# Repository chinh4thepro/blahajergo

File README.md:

## Hardware
Uses a Nice!Nano V2 (or any compatible microcontroller) as the MCU

Parts list:
- 56x SOD-123 (supports through holes too) 1N4148W diodes
- 56x Kailh 1350 Hotswap Sockets
- 56x Kailh choc v1 or v2 switches (v1's may be a little loose)
- 54x 1u choc keycaps
- 2x 1.5u choc keycaps
- 2x Nice!Nano V2 (sockets too)
- 2x 0.91in 128x32 SSD1306 OLED displays (sockets too)
- 2x 110mAh 301230 lithium batteries with PH 2.00mm connectors
- 2x Alps miniature SPDT switches
- 2x JST PH 2.00mm battery connectors
- 2x Panasonic EVQPUC buttons

## Software
Keymap based/inspired by FlatFootFox's (ImStuBTW) [TypeBoy MKII](https://github.com/ImStuBTW/typeboy_mkii)

Config can be found [here](https://github.com/chinh4thepro/zmk-config-blahajergo/tree/master)

## Design
Planned to have a 3d-printed case and acrylic case.

Traced blahaj image in courtesy of [Sheepy0125](https://github.com/sheepy0125)

## Progress
- [x] Design schematic - Done 2/10/2024
- [x] Name + Logo - Done 2/5/2024
- [x] Design PCB - Done 2/10/2024
- [x] Redesign PCB - Done 5/08/2024
- [x] Order PCB + Parts - Done 2/12/2024
- [x] Reorder PCB - Done 5/9/2024
- [x] Construct PCB - Done 5/17/2024
- [x] Port to ZMK - Done 2/27/2024
- [ ] Design 3d case
- [ ] Design acrylic case

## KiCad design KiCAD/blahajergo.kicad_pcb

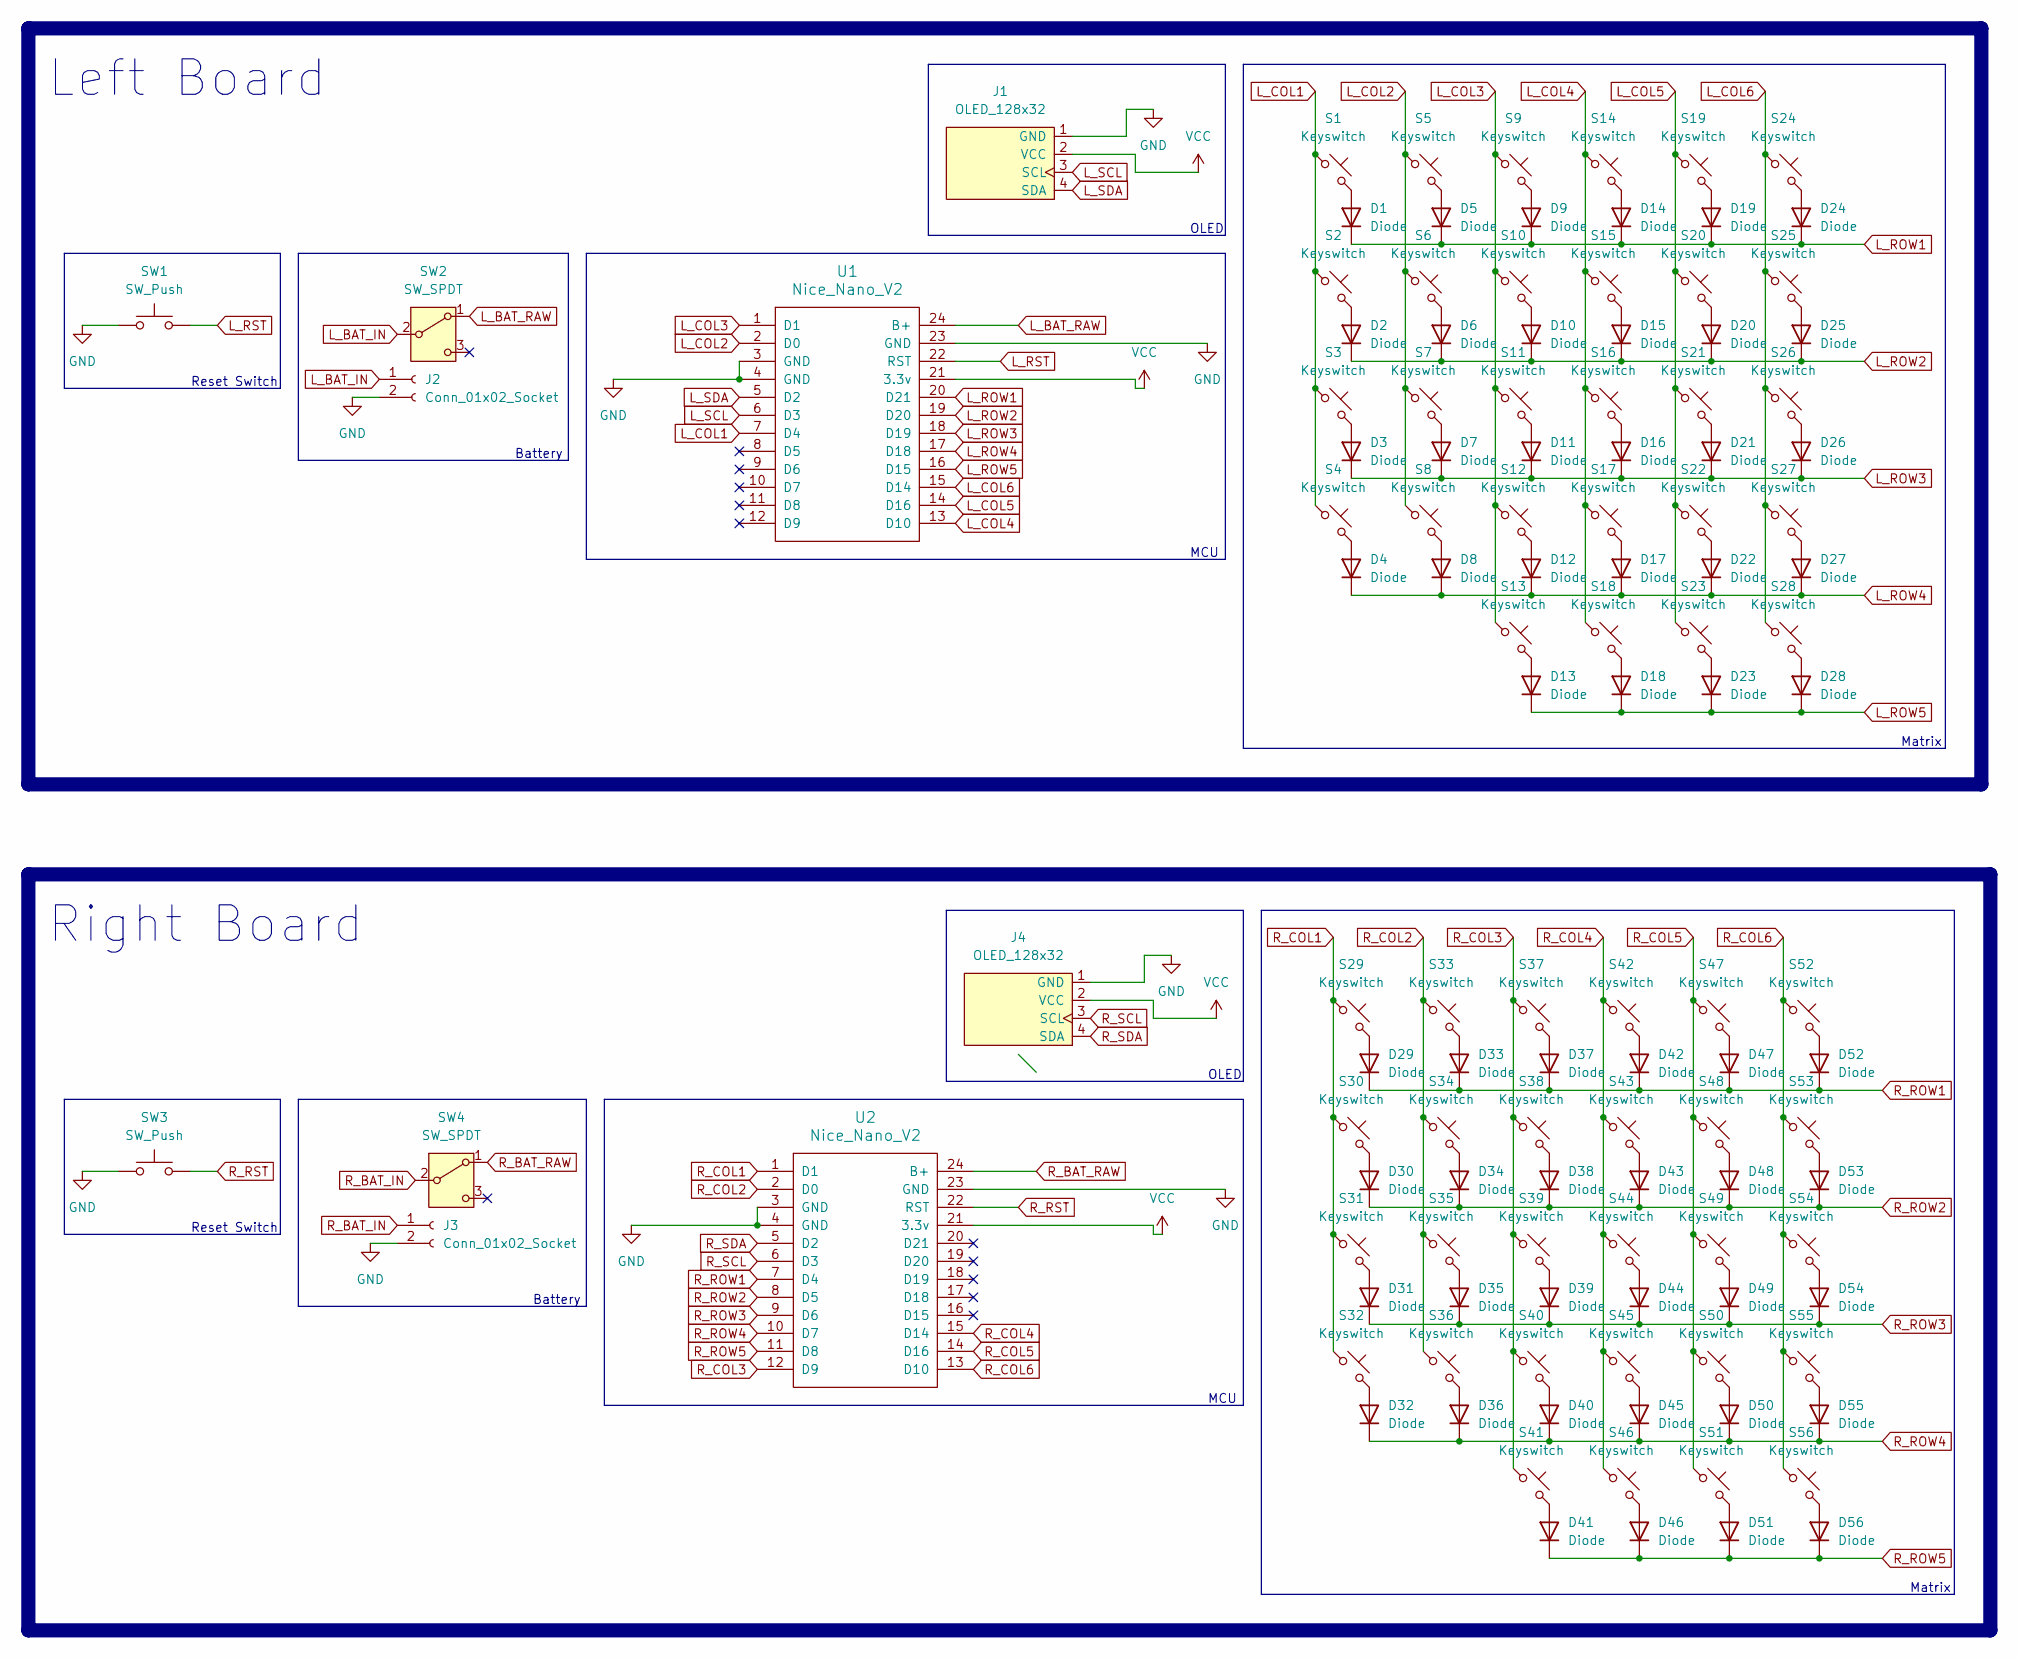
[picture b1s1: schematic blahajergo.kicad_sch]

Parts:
D1, D2, D3, D4, D5, D6, D7, D8, D9, D10, D11, D12, D13, D14, D15, D16, D17, D18, D19, D20, D21, D22, D23, D24, D25, D26, D27, D28, D29, D30, D31, D32, D33, D34, D35, D36, D37, D38, D39, D40, D41, D42, D43, D44, D45, D46, D47, D48, D49, D50, D51, D52, D53, D54, D55, D56: Diode; ComboDiode
J1, J4: OLED_128x32
J2, J3: Conn_01x02_Socket; JST_PH_S2B-PH-K_1x02_P2.00mm_Horizontal
S1, S2, S3, S4, S5, S6, S7, S8, S9, S10, S11, S12, S13, S14, S15, S16, S17, S18, S19, S20, S21, S22, S23, S24, S25, S26, S27, S28, S29, S30, S31, S32, S33, S34, S35, S36, S37, S38, S39, S40, S41, S42, S43, S44, S45, S46, S47, S48, S49, S50, S51, S52, S53, S54, S55, S56: Keyswitch; Hotswap_Choc_V1V2
SW1, SW3: SW_Push; Panasonic_EVQPUL_EVQPUC
SW2, SW4: SW_SPDT; SPDT_C128955
U1, U2: Nice_Nano_V2; Nice_Nano_V2_Flipped

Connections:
GND: J1.1 (GND), J2.2, J3.2, J4.1 (GND), SW1.1, SW3.1, U1.3 (GND), U1.4 (GND), U1.23 (GND), U2.3 (GND), U2.4 (GND), U2.23 (GND)
L_BAT_IN: J2.1, SW2.2 (B)
L_BAT_RAW: SW2.1 (A), U1.24 (B+)
L_COL1: S1.1, S2.1, S3.1, S4.1, U1.7 (D4)
L_COL2: S5.1, S6.1, S7.1, S8.1, U1.2 (D0)
L_COL3: S9.1, S10.1, S11.1, S12.1, S13.1, U1.1 (D1)
L_COL4: S14.1, S15.1, S16.1, S17.1, S18.1, U1.13 (D10)
L_COL5: S19.1, S20.1, S21.1, S22.1, S23.1, U1.14 (D16)
L_COL6: S24.1, S25.1, S26.1, S27.1, S28.1, U1.15 (D14)
L_ROW1: D1.1 (K), D5.1 (K), D9.1 (K), D14.1 (K), D19.1 (K), D24.1 (K), U1.20 (D21)
L_ROW2: D2.1 (K), D6.1 (K), D10.1 (K), D15.1 (K), D20.1 (K), D25.1 (K), U1.19 (D20)
L_ROW3: D3.1 (K), D7.1 (K), D11.1 (K), D16.1 (K), D21.1 (K), D26.1 (K), U1.18 (D19)
L_ROW4: D4.1 (K), D8.1 (K), D12.1 (K), D17.1 (K), D22.1 (K), D27.1 (K), U1.17 (D18)
L_ROW5: D13.1 (K), D18.1 (K), D23.1 (K), D28.1 (K), U1.16 (D15)
L_RST: SW1.2, U1.22 (RST)
L_SCL: J1.3 (SCL), U1.6 (D3)
L_SDA: J1.4 (SDA), U1.5 (D2)
unnamed: D1.2 (A), S1.2
unnamed: D2.2 (A), S2.2
unnamed: D3.2 (A), S3.2
unnamed: D4.2 (A), S4.2
unnamed: D5.2 (A), S5.2
unnamed: D6.2 (A), S6.2
unnamed: D7.2 (A), S7.2
unnamed: D8.2 (A), S8.2
unnamed: D9.2 (A), S9.2
unnamed: D10.2 (A), S10.2
unnamed: D11.2 (A), S11.2
unnamed: D12.2 (A), S12.2
unnamed: D13.2 (A), S13.2
unnamed: D14.2 (A), S14.2
unnamed: D15.2 (A), S15.2
unnamed: D16.2 (A), S16.2
unnamed: D17.2 (A), S17.2
unnamed: D18.2 (A), S18.2
unnamed: D19.2 (A), S19.2
unnamed: D20.2 (A), S20.2
unnamed: D21.2 (A), S21.2
unnamed: D22.2 (A), S22.2
unnamed: D23.2 (A), S23.2
unnamed: D24.2 (A), S24.2
unnamed: D25.2 (A), S25.2
unnamed: D26.2 (A), S26.2
unnamed: D27.2 (A), S27.2
unnamed: D28.2 (A), S28.2
unnamed: D29.2 (A), S29.2
unnamed: D30.2 (A), S30.2
unnamed: D31.2 (A), S31.2
unnamed: D32.2 (A), S32.2
unnamed: D33.2 (A), S33.2
unnamed: D34.2 (A), S34.2
unnamed: D35.2 (A), S35.2
unnamed: D36.2 (A), S36.2
unnamed: D37.2 (A), S37.2
unnamed: D38.2 (A), S38.2
unnamed: D39.2 (A), S39.2
unnamed: D40.2 (A), S40.2
unnamed: D41.2 (A), S41.2
unnamed: D42.2 (A), S42.2
unnamed: D43.2 (A), S43.2
unnamed: D44.2 (A), S44.2
unnamed: D45.2 (A), S45.2
unnamed: D46.2 (A), S46.2
unnamed: D47.2 (A), S47.2
unnamed: D48.2 (A), S48.2
unnamed: D49.2 (A), S49.2
unnamed: D50.2 (A), S50.2
unnamed: D51.2 (A), S51.2
unnamed: D52.2 (A), S52.2
unnamed: D53.2 (A), S53.2
unnamed: D54.2 (A), S54.2
unnamed: D55.2 (A), S55.2
unnamed: D56.2 (A), S56.2
R_BAT_IN: J3.1, SW4.2 (B)
R_BAT_RAW: SW4.1 (A), U2.24 (B+)
R_COL1: S29.1, S30.1, S31.1, S32.1, U2.1 (D1)
R_COL2: S33.1, S34.1, S35.1, S36.1, U2.2 (D0)
R_COL3: S37.1, S38.1, S39.1, S40.1, S41.1, U2.12 (D9)
R_COL4: S42.1, S43.1, S44.1, S45.1, S46.1, U2.15 (D14)
R_COL5: S47.1, S48.1, S49.1, S50.1, S51.1, U2.14 (D16)
R_COL6: S52.1, S53.1, S54.1, S55.1, S56.1, U2.13 (D10)
R_ROW1: D29.1 (K), D33.1 (K), D37.1 (K), D42.1 (K), D47.1 (K), D52.1 (K), U2.7 (D4)
R_ROW2: D30.1 (K), D34.1 (K), D38.1 (K), D43.1 (K), D48.1 (K), D53.1 (K), U2.8 (D5)
R_ROW3: D31.1 (K), D35.1 (K), D39.1 (K), D44.1 (K), D49.1 (K), D54.1 (K), U2.9 (D6)
R_ROW4: D32.1 (K), D36.1 (K), D40.1 (K), D45.1 (K), D50.1 (K), D55.1 (K), U2.10 (D7)
R_ROW5: D41.1 (K), D46.1 (K), D51.1 (K), D56.1 (K), U2.11 (D8)
R_RST: SW3.2, U2.22 (RST)
R_SCL: J4.3 (SCL), U2.6 (D3)
R_SDA: J4.4 (SDA), U2.5 (D2)
VCC: J1.2 (VCC), J4.2 (VCC), U1.21 (3.3v), U2.21 (3.3v)

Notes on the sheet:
OLED
Right Board
MCU
Battery
Reset Switch
Left Board
Matrix

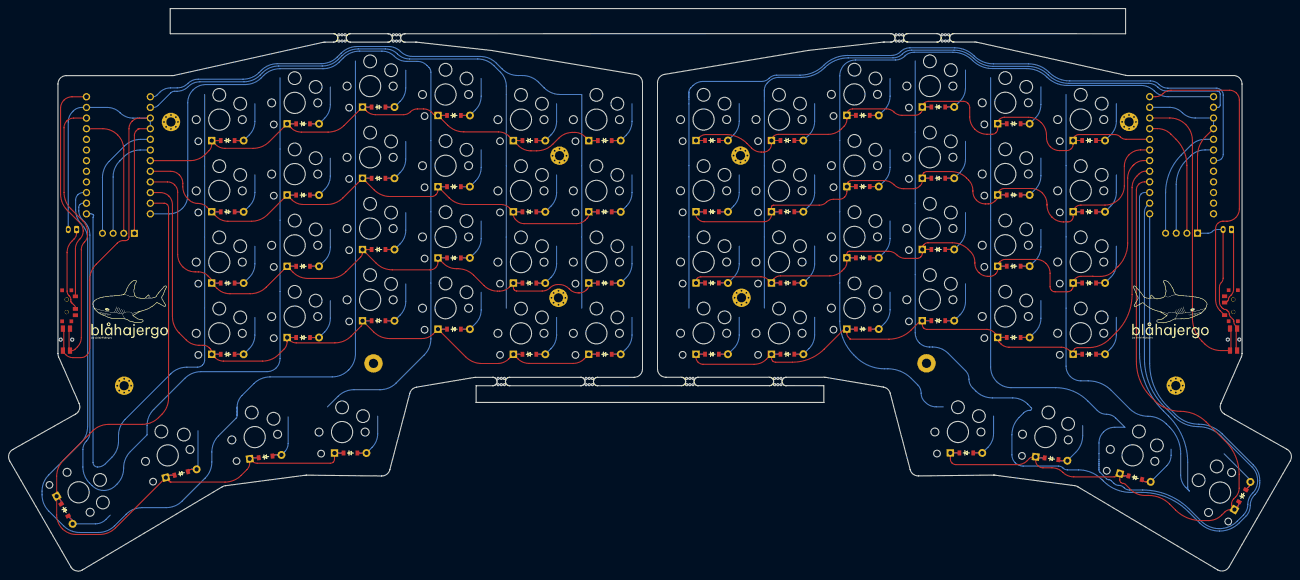
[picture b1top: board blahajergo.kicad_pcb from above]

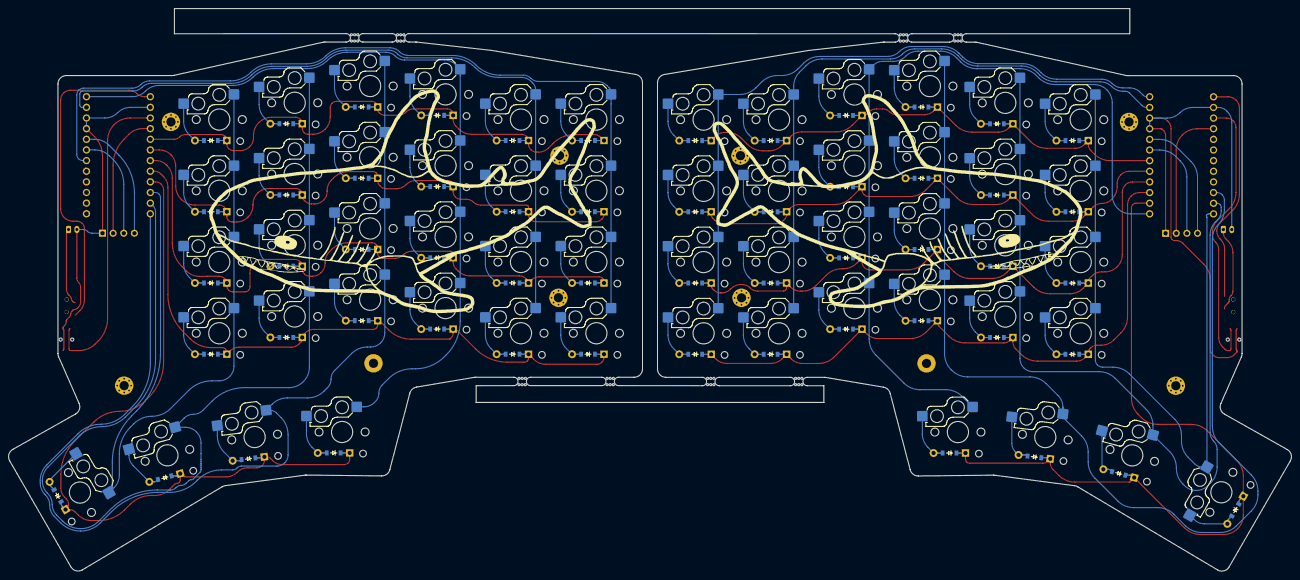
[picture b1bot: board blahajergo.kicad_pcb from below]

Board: 2 copper layers, 306.1 x 134.2 mm, 138 parts (6 on the bottom side), 90 nets.

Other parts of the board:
_6, _6#2, _6#3, _6#4, _6#5, _6#6, _6#7, _6#8: MountingHole_2.2mm_M2_Pad_Via
mouse-bite-2mm-slot, mouse-bite-2mm-slot#2, mouse-bite-2mm-slot#3, mouse-bite-2mm-slot#4, mouse-bite-2mm-slot#5, mouse-bite-2mm-slot#6, mouse-bite-2mm-slot#7, mouse-bite-2mm-slot#8: VAL**; mouse-bite-2mm-slot

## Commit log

2024-02-06 add pcbs
2024-02-10 make shematic and condense into one file
2024-02-11 add mousebites
2024-02-12 cleanup
2024-02-12 add git-ignore
2024-02-12 update gitignore
2024-02-13 fix readme
2024-02-13 update OLED model name
2024-02-24 Initial User Config.
2024-02-25 add blahajergo shield
2024-02-25 forgot a semi-colon
2024-02-25 forgot semi-colon again
2024-02-25 go back!
2024-02-25 fix gpio
2024-02-25 oops
2024-02-25 remove stuff
2024-02-25 TYPO
2024-02-26 started on keymap
2024-02-26 zmk configuration submodule
2024-02-26 remove backups
2024-02-26 remove text
2024-02-27 add images
2024-02-27 REDO: Fix MCU orientation, add support for both choc v1 + v2, new graphics, and new reset switch
2024-02-27 clean up
2024-02-27 add left alt to keymap lol
2024-02-28 finish keymap
2024-02-28 update .gitignore again
2024-02-28 oopsies
2024-02-28 remove submodule
2024-02-28 submodule :thumbsup:
2024-02-28 update readme... again
2024-02-28 update parts list
2024-02-28 jacks is a bit weird
2024-02-28 don't really like this line
2024-02-28 wrong numbers lol
2024-04-04 aaaa
2024-04-04 remove stuff from gitignore
2024-04-04 use previous working pcb design
2024-05-09 finally finish pcb redo
2024-05-09 production files
2024-05-19 flip jst connector terminals
2024-05-19 update goal thingy
2024-05-19 straigten
